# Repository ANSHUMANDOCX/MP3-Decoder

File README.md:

# MP3 Player

This is a Portable MP3 player which allows one to play music on the even at places where there is no internet access.
You can also view almost all the details you would require while listenting to music on the OLED dispaly that will be connected to it.
Also has a capbility to be programmed using a Arduino or a FTDI programmer.

**Untested Firmware**

Features-
- Atmega328p as a MCU
- DF player MINI (DFR0299) as a MP3 decoder(since i already had it lying around)
- 128x64 0.96 inch OLED display for UI
- Inbuilt charging using TP4056
- 4 iterfacing buttons Play/Pause  Prev/Vol-  Next/Vol+ and RESET for the board 
- Onboard leds for debugging,Power,Charging and Playing status

## Notes for V2 + last minute changes 
- The temp pin of the tp4056 ic needs to be grounded instead of being left open since it puss that pin to a random value and doesnt allow the battery to be charged
- i need to route the next and prev buttons to one of the io pins of the atmega chip since earlier i had it on the adkey mode of the df player which when pressed puts board in a where it no longer receives commands from the mcu
- one of the most obvious this i missed is adding a switch to turn off the 5v from the boost ic directly since now whenever i charge the board the board stays on permanently so to overcome that i have temporarily added button combination to put the df player to sleep.
- in the image u can see that ive added jumpers to the board for connecting the pay pause button to the mcu directly.

# PCB Schematic and CAD

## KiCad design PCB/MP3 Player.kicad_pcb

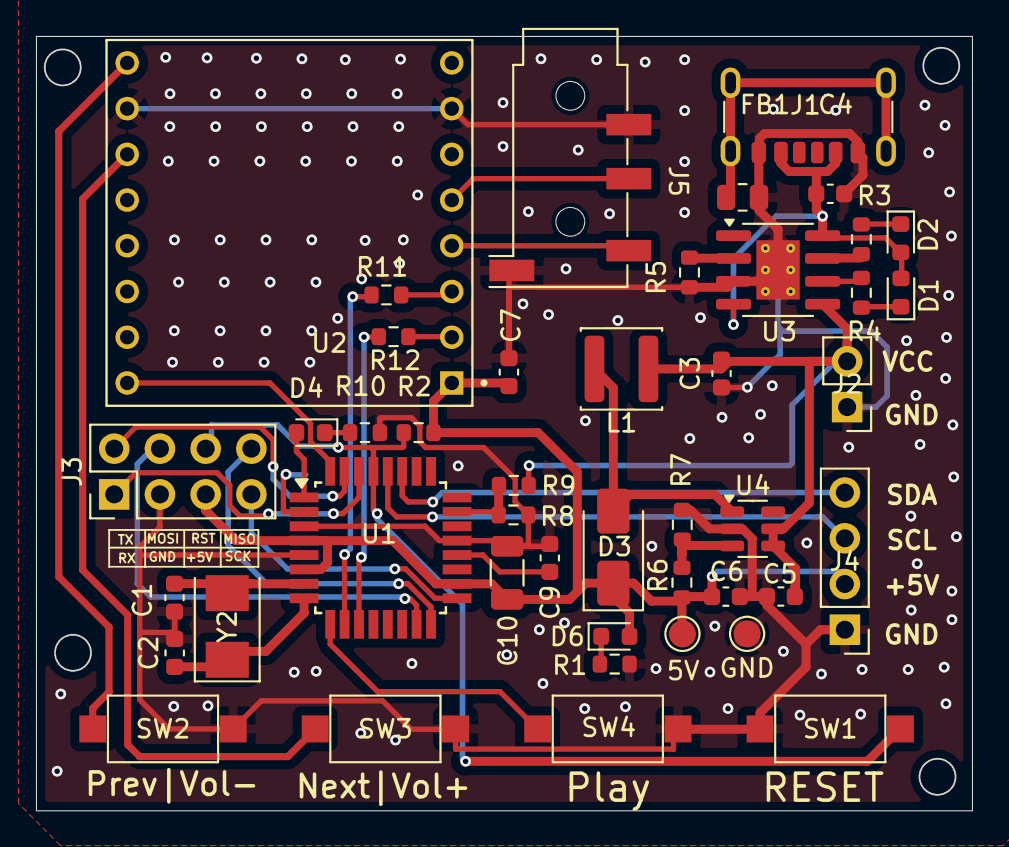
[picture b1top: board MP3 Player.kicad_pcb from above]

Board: 2 copper layers, 52.0 x 43.0 mm, 45 parts (1 on the bottom side), 37 nets.

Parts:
5V: TestPoint_Pad_D1.5mm
C1, C2: 22pf; C_0603_1608Metric
C3, C4: 10uf; C_0603_1608Metric
C5, C6: 22uf; C_0603_1608Metric
C7, C9: 0.1uf; C_0603_1608Metric
C10: 100uf; C_1206_3216Metric
D1, D2, D4, D6: LED; LED_0603_1608Metric
D3: SS34; D_SMA
FB1: FerriteBead_Small; R_0805_2012Metric
GND: TestPoint_Pad_D1.5mm
GND#2: TestPoint_Pad_D1.0mm
J1: USB_C_Receptacle_PowerOnly_6P; USB_C_Receptacle_GCT_USB4125-xx-x_6P_TopMnt_Horizontal
J2: BAT; PinHeader_1x02_P2.54mm_Vertical
J3: Conn_02x04_Counter_Clockwise; PinHeader_2x04_P2.54mm_Vertical
J4: OLED; PinHeader_1x04_P2.54mm_Vertical
J5: AudioJack4; Jack_3.5mm_KoreanHropartsElec_PJ-320D-4A_Horizontal
L1: L; L_APV_ANR4030
R1: 100R; R_0603_1608Metric
R2: 10k; R_0603_1608Metric
R3, R4, R10, R11, R12: 1k; R_0603_1608Metric
R5: 1.2k; R_0603_1608Metric
R6: 750k; R_0603_1608Metric
R7, R8, R9: 100k; R_0603_1608Metric
SW1: SW_Push; SW_SPST_CK_RS282G05A3
SW2: SW_Prev/Vol -; SW_SPST_CK_RS282G05A3
SW3: SW_Next/Vol+; SW_SPST_CK_RS282G05A3
SW4: Play/Pause; SW_SPST_CK_RS282G05A3
U1: ATmega328P-A; TQFP-32_7x7mm_P0.8mm
U2: DFR0299; MODULE_DFR0299
U3: TP4056-42-ESOP8; SOIC-8-1EP_3.9x4.9mm_P1.27mm_EP2.41x3.3mm_ThermalVias
U4: MT3608; SOT-23-6
Y2: 16 Mhz; Crystal_SMD_5032-2Pin_5.0x3.2mm

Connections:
+5V: 5V.1, C6.1, C7.1, C10.1, D3.1 (K), D6.2 (A), J3.5, J4.2, R2.1, R6.2, U1.4 (VCC), U1.6 (VCC), U1.18 (AVCC), U2.1 (VCC)
+BATT: C3.1, C5.1, J2.2, L1.1, R9.1, U3.5 (BAT), U4.4 (EN), U4.5 (IN)
ADC: R8.1, R9.2, U1.23 (PC0)
GND: C1.2, C2.1, C3.2, C4.2, C5.2, C6.2, C7.2, C9.1, C10.2, FB1.2, GND.1, GND#2.1, J1.A12 (GND), J1.B12 (GND), J2.1, J3.3, J4.1, J5.R2, J5.S, R1.2, R5.1, R7.1, R8.2, R10.1, SW1.2, SW2.1, SW3.1, SW4.2, U1.3 (GND), U1.5 (GND), U1.21 (GND), U2.7 (GND), U2.10 (GND__1), U3.3 (GND), U3.9 (EPAD), U4.2 (GND)
MISO: J3.8, U1.16 (PB4)
MOSI: J3.4, U1.15 (PB3)
unnamed: D1.1 (K), R4.1
unnamed: D2.1 (K), R3.2
unnamed: D3.2 (A), L1.2, U4.1 (SW)
unnamed: D4.2 (A), U1.1 (PD3)
unnamed: D4.1 (K), R10.2
unnamed: D6.1 (K), R1.1
unnamed: FB1.1, J1.S1 (SHIELD)
unnamed: C9.2, U1.20 (AREF)
unnamed: SW4.1, U1.9 (PD5)
unnamed: C1.1, U1.7 (XTAL1/PB6), Y2.2
unnamed: C2.2, U1.8 (XTAL2/PB7), Y2.1
unnamed: J5.R1, U2.5 (DAC_L)
unnamed: J5.T, U2.4 (DAC_R)
unnamed: SW2.2, U2.9 (IO1)
unnamed: SW3.2, U2.11 (IO2)
unnamed: R12.1, U2.2 (RX)
unnamed: R11.1, U2.3 (TX)
unnamed: R5.2, U3.2 (PROG)
unnamed: R3.1, U3.7 (~CHRG)
unnamed: R4.2, U3.6 (~STDBY)
unnamed: R6.1, R7.2, U4.3 (FB)
RST: J3.6, R2.2, SW1.1, U1.29 (~RESET/PC6)
RX: R11.2, U1.10 (PD6)
RX0: J3.1, U1.30 (PD0)
SCK: J3.7, U1.17 (PB5)
SCL: J4.3, U1.28 (PC5)
SDA: J4.4, U1.27 (PC4)
STATUS: U1.32 (PD2), U2.16 (BUSY)
TX: R12.2, U1.11 (PD7)
TX0: J3.2, U1.31 (PD1)
VBUS: C4.1, D1.2 (A), D2.2 (A), J1.A9 (VBUS), J1.B9 (VBUS), U3.4 (V_{CC}), U3.8 (CE)

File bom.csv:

Designator,Footprint,Quantity,Value,LCSC Part #
"C1, C2",0603,2,22pf,
C10,1206,1,100uf,
"C3, C4",0603,2,10uf,
"C5, C6",0603,2,22uf,
"C7, C9",0603,2,0.1uf,
"D1, D2, D4, D6",0603,4,LED,
D3,D_SMA,1,SS34,
FB1,0805,1,FerriteBead_Small,
J1,USB_C_Receptacle_GCT_USB4125-xx-x_6P_TopMnt_Horizontal,1,USB_C_Receptacle_PowerOnly_6P,
J2,PinHeader_1x02_P2.54mm_Vertical,1,BAT,
J3,PinHeader_2x04_P2.54mm_Vertical,1,Conn_02x04_Counter_Clockwise,
J4,PinHeader_1x04_P2.54mm_Vertical,1,OLED,
J5,Jack_3.5mm_KoreanHropartsElec_PJ-320D-4A_Horizontal,1,AudioJack4,
L1,L_APV_ANR4030,1,L,
R1,0603,1,100R,
"R10, R11, R12, R3, R4",0603,5,1k,
R2,0603,1,10k,
R5,0603,1,1.2k,
R6,0603,1,750k,
"R7, R8, R9",0603,3,100k,
SW1,SW_SPST_CK_RS282G05A3,1,SW_Push,
SW2,SW_SPST_CK_RS282G05A3,1,SW_Prev/Vol -,
SW3,SW_SPST_CK_RS282G05A3,1,SW_Next/Vol+,
SW4,SW_SPST_CK_RS282G05A3,1,Play/Pause,
U1,TQFP-32_7x7mm_P0.8mm,1,ATmega328P-A,
U2,MODULE_DFR0299,1,DFR0299,
U3,SOIC-8-1EP_3.9x4.9mm_P1.27mm_EP2.41x3.3mm_ThermalVias,1,TP4056-42-ESOP8,
U4,SOT-23-6,1,MT3608,
Y2,Crystal_SMD_5032-2Pin_5.0x3.2mm,1,16 Mhz,

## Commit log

2025-10-26 Create README.md for MP3 Player project
    Added a README file for the MP3 Player project with features and images.
2025-10-26 Document untested firmware and features in README
    Added section for untested firmware and features.
2025-10-26 Create CAD
